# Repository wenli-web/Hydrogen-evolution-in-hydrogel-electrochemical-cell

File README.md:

# Hydrogen evolution in hydrogel electrochemical cell
This is a repository for paper "Hydrogen Evolution and Dynamics in Hydrogel Electrochemical Cells for Ischemia-Reperfusion therapy".

This repo contains 
1. A flexible PCB designed for delivering constant current to the hydrogen producing device.
2. A user interface software code for wirelessly controlling the flexible PCB.
3. A code to plot hydrogen diffusion simulation data.
4. A code to analyze the hydrogen evolution video.

# System requirements
1. The flexible PCB design requires the installation of software KiCad 8.0 (https://www.kicad.org/download/). We use windows 64 bit system. The computer system requirements can be seen in https://www.kicad.org/help/system-requirements/.
2. The running of all the python scripts requires the installment of a few Python packages: pygame, asyncio, platform, bleak, struct, pandas, numpy, matplotlib, and cv2. Install time of all the packages would take 10-20 min.
3. All the python scripts have been tested in Windows 11.

# Instruction
1. The implement of video analysis code and heat map code is performed on Jupyter notebook. The installment of Jupyter notebook can be found here: https://jupyter.org/install.
2. The original videos and simulation data are included in corresponding folders for reproduction of the result.
3. The implement of Bluetooth user interface is performed on Spyder (https://www.spyder-ide.org/) with python 3.13. The running of the user interface codes requires the flexible PCB to be turned on.
4. The expected run time for demo with provided data on a "normal" desktop computer would be below 1 min.
5. The expected output for video and simulation data analysis is also included in corresponding folders for reference.

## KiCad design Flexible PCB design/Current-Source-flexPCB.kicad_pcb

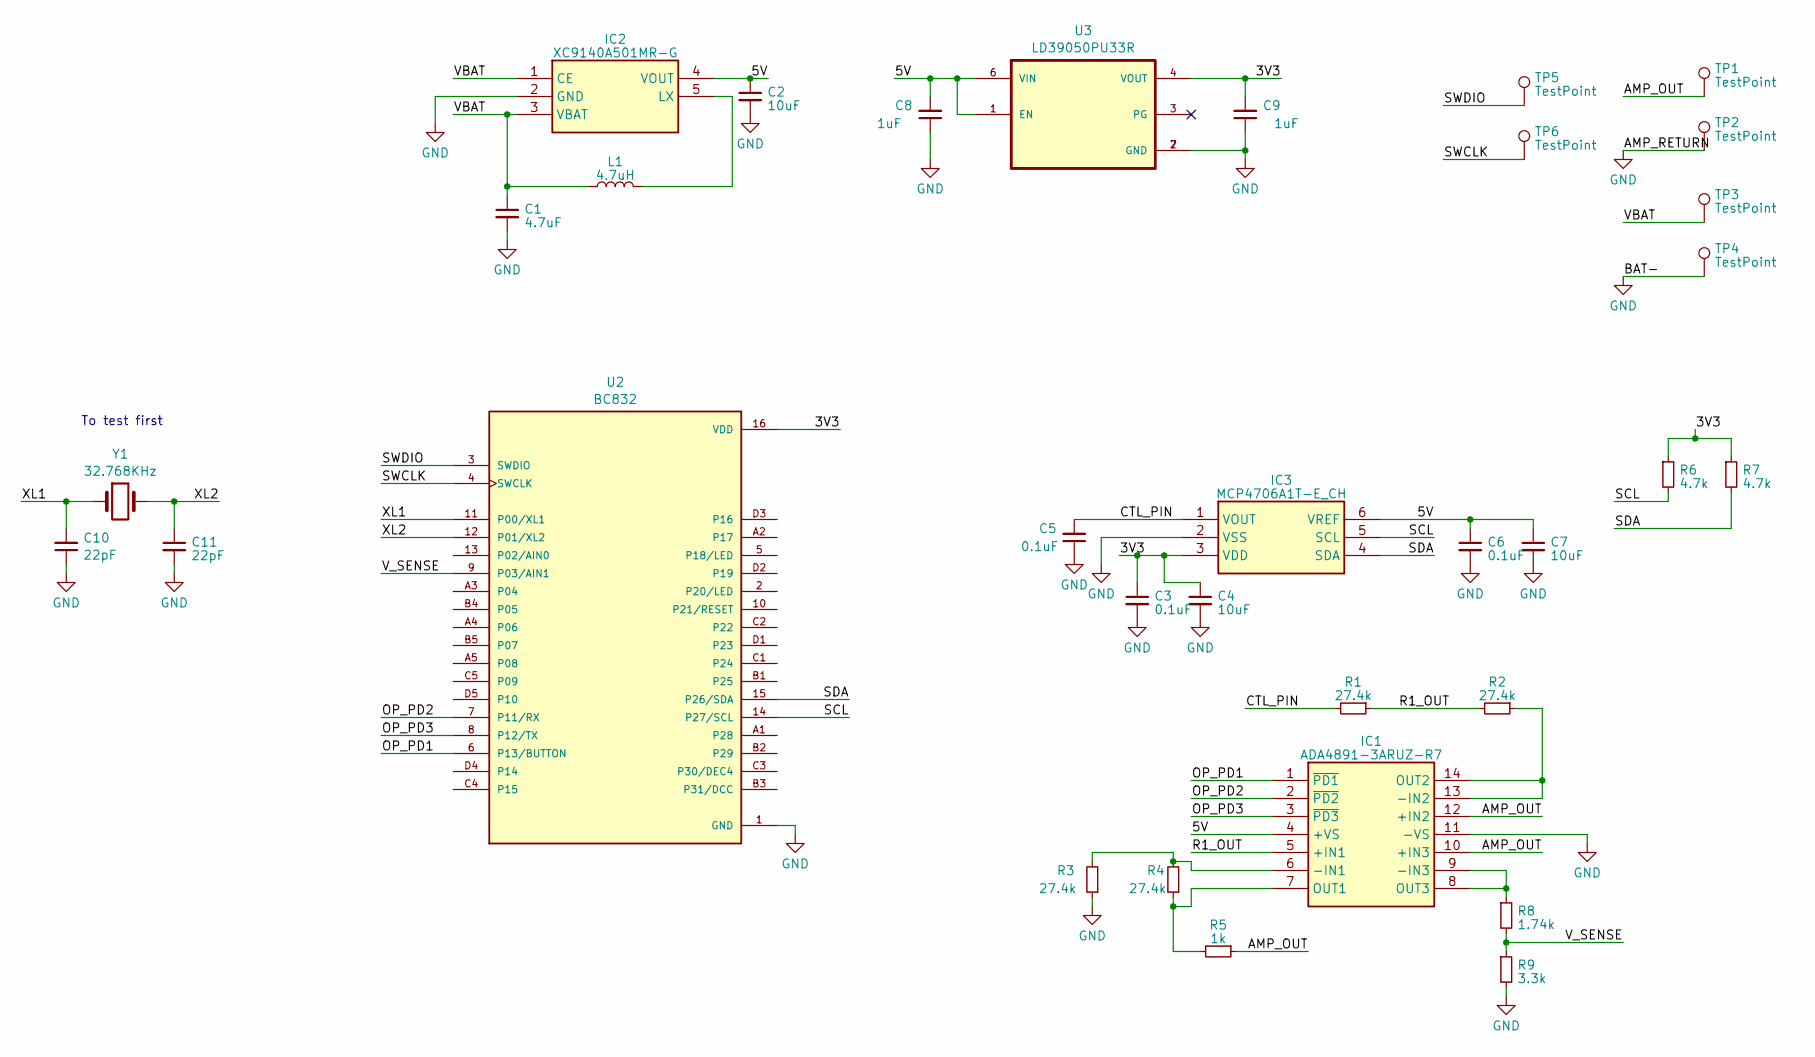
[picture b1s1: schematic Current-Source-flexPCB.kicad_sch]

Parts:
C1: 4.7uF; C_0603_1608Metric; Part# LMK107BJ475MAHT
C2, C4, C7: 10uF; C_0603_1608Metric; Part# LMK107BJ106MA
C3, C5, C6: 0.1uF; C_0603_1608Metric; Part# C0603C104K3RAC7411
C8, C9: 1uF; C_0603_1608Metric
C10, C11: 22pF; C_0603_1608Metric
IC1: ADA4891-3ARUZ-R7; SOP65P640X120-14N; Mouser Part Number 584-ADA4891-3ARUZ-R7
IC2: XC9140A501MR-G; SOT-25-5; Mouser Part Number 865-XC9140A501MR-G
IC3: MCP4706A1T-E_CH; SOT-23-6; Mouser Part Number 579-MCP4706A1TECH
L1: 4.7uH; L_1008_2520Metric
R1, R2, R3, R4: 27.4k; R_0603_1608Metric; Part# RT0603DRE0727K4L
R5: 1k; R_0603_1608Metric; Part# RT0603DRE0727K4L
R6, R7: 4.7k; R_0603_1608Metric; Part# RT0603FRE074K7L
R8: 1.74k; R_0603_1608Metric; Part# RT0603DRE0727K4L
R9: 3.3k; R_0603_1608Metric; Part# RT0603DRE0727K4L
TP1, TP2, TP3, TP4, TP5, TP6: TestPoint; TestPoint_Pad_D1.0mm
U2: BC832; MODULE_BC832; PARTREV 2.02
U3: LD39050PU33R; SON95P300X300X100-7N
Y1: 32.768KHz; Crystal_SMD_3215-2Pin_3.2x1.5mm

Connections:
/3V3: C3.1, C4.1, C9.2, IC3.3 (VDD), R6.1, R7.1, U2.16 (VDD), U3.4 (VOUT)
/5V: C2.1, C6.1, C7.1, C8.2, IC1.4 (+VS), IC2.4 (VOUT), IC3.6 (VREF), U3.1 (EN), U3.6 (VIN)
/AMP_OUT: IC1.10 (+IN3), IC1.12 (+IN2), R5.1, TP1.1
/CTL_PIN: C5.2, IC3.1 (VOUT), R1.2
/OP_PD1: IC1.1 (~PD1), U2.6 (P13/BUTTON)
/OP_PD2: IC1.2 (~PD2), U2.7 (P11/RX)
/OP_PD3: IC1.3 (~PD3), U2.8 (P12/TX)
/R1_OUT: IC1.5 (+IN1), R1.1, R2.2
/SCL: IC3.5 (SCL), R6.2, U2.14 (P27/SCL)
/SDA: IC3.4 (SDA), R7.2, U2.15 (P26/SDA)
/SWCLK: TP6.1, U2.4 (SWCLK)
/SWDIO: TP5.1, U2.3 (SWDIO)
/VBAT: C1.1, IC2.1 (CE), IC2.3 (VBAT), L1.1, TP3.1
/V_SENSE: R8.2, R9.1, U2.9 (P03/AIN1)
/XL1: C10.2, U2.11 (P00/XL1), Y1.1
/XL2: C11.1, U2.12 (P01/XL2), Y1.2
GND: C1.2, C2.2, C3.2, C4.2, C5.1, C6.2, C7.2, C8.1, C9.1, C10.1, C11.2, IC1.11 (-VS), IC2.2 (GND), IC3.2 (VSS), R3.1, R9.2, TP2.1, TP4.1, U2.1 (GND), U3.2 (GND), U3.7 (GND)
unnamed: IC1.6 (-IN1), R3.2, R4.2
unnamed: IC1.13 (-IN2), IC1.14 (OUT2), R2.1
unnamed: IC1.8 (OUT3), IC1.9 (-IN3), R8.1
unnamed: IC1.7 (OUT1), R4.1, R5.2
unnamed: IC2.5 (LX), L1.2

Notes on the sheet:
To test first

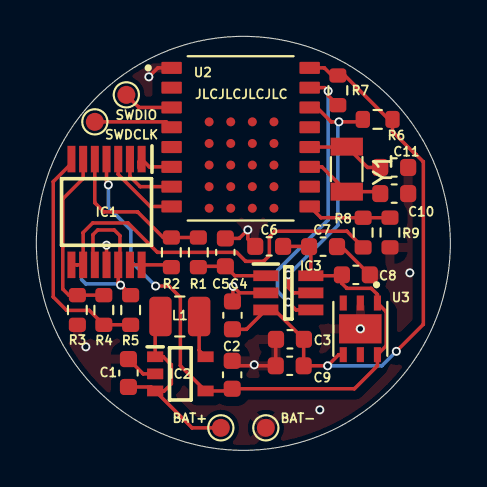
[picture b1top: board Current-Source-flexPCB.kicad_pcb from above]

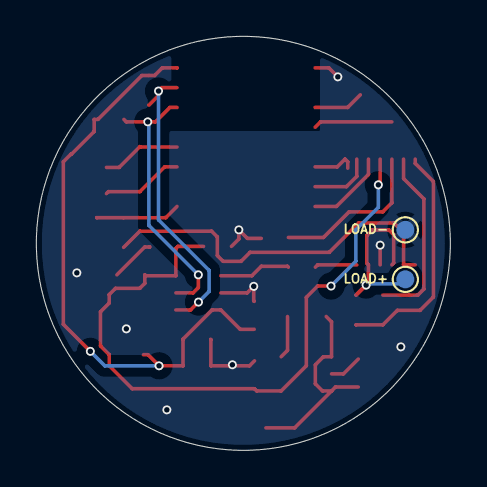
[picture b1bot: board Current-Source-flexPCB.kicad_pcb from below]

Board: 2 copper layers, 23.0 x 23.0 mm, 33 parts (2 on the bottom side), 22 nets.
